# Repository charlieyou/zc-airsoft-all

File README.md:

# zc-airsoft-all

every design file from zc-airsoft, now open source

banshee lite circuit still needs some modifications to work, mainly adding resistors to fix outputs receiving conflicting input

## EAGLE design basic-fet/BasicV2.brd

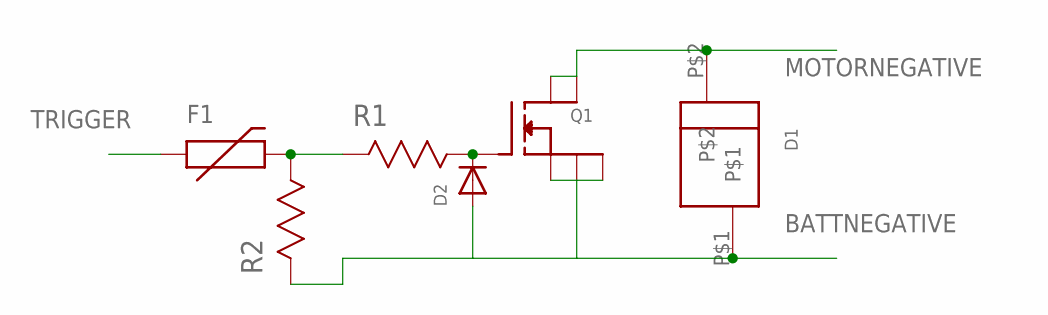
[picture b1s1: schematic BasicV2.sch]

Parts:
D1: 5.0SMDJ24ASMD; DO-214AB
D2: DIODESOD-123; SOD-123
F1: PTCSMD; PTC-1206
Q1: PSMN039LFPAC; LFPAC
R1: 100 Ohm; RESC3216X71N
R2: 220 Ohm; RESC6332X71N

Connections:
BATTNEGATIVE: D1.P$1, D2.A, Q1.1 (S1), Q1.2 (S2), Q1.3 (S3), R2.2 (R2)
MOTORNEGATIVE: D1.P$2, Q1.5 (D1), Q1.6 (D2)
unnamed: D2.C, Q1.4 (G), R1.1 (R1)
unnamed: F1.2, R1.2 (R2), R2.1 (R1)
TRIGGER: F1.1

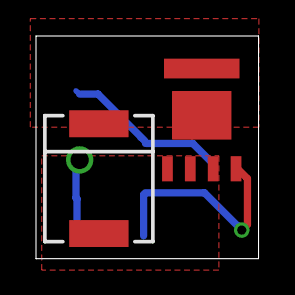
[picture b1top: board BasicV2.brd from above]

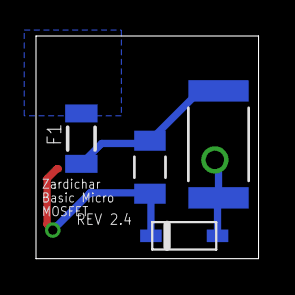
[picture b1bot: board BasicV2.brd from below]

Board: 2 copper layers, 12.4 x 12.4 mm, 6 parts (4 on the bottom side), 4 nets.

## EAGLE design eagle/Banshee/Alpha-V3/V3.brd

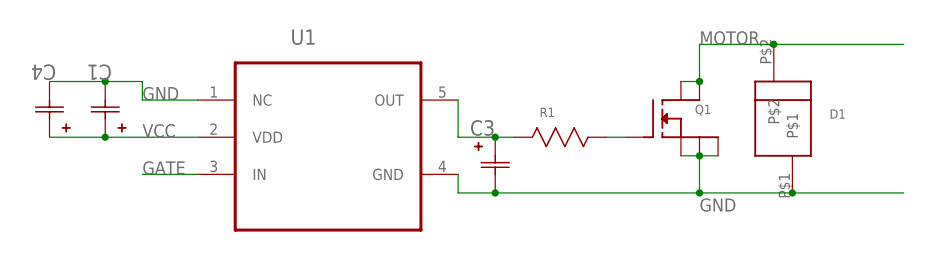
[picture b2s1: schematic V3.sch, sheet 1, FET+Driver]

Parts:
C1: 1UF; CAPC3216X127N
C3: 1uF; CAPC1608X94N
C4: 0.1UF; CAPC1608X90N
D1: 5.0SMDJ24ASMD; DO-214AB
Q1: PSMN039LFPAC; LFPAC; MPN PSMN0R9-25YLC,115
R1: 100 Ohm; RESC1608X60N
U1: NCS2001SN1T1G; SOT95P275X110-5N

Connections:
GATE: U1.3 (IN); also elsewhere on the board
GND: C1.2 (C2), C3.2 (C2), C4.2 (C2), D1.P$1, Q1.1 (S1), Q1.2 (S2), Q1.3 (S3), U1.1 (NC), U1.4 (GND); also elsewhere on the board
MOTOR: D1.P$2, Q1.5 (D1), Q1.6 (D2); also elsewhere on the board
unnamed: Q1.4 (G), R1.1 (R1)
unnamed: C3.1 (C1), R1.2 (R2), U1.5 (OUT)
VCC: C1.1 (C1), C4.1 (C1), U1.2 (VDD); also elsewhere on the board

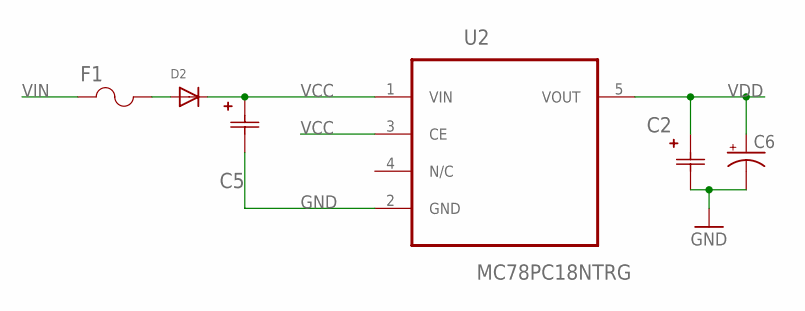
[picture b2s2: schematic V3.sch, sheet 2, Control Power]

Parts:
C2: 2200pF; CAPC1608X90N
C5: 220UF; CAPCP7343X430N
C6: 150uF; EIA3528
D2: DIODESOD-123; SOD-123
F1: F1206B3R00FWTR; FUSM3216X140N
U2: MC78PC18NTRG; SOT95P275X110-5N

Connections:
GND: C2.2 (C2), C5.2 (C2), C6.C (-), U2.2 (GND); also elsewhere on the board
unnamed: D2.A, F1.2
VCC: C5.1 (C1), D2.C, U2.1 (VIN), U2.3 (CE); also elsewhere on the board
VDD: C2.1 (C1), C6.A (+), U2.5 (VOUT); also elsewhere on the board
VIN: F1.1

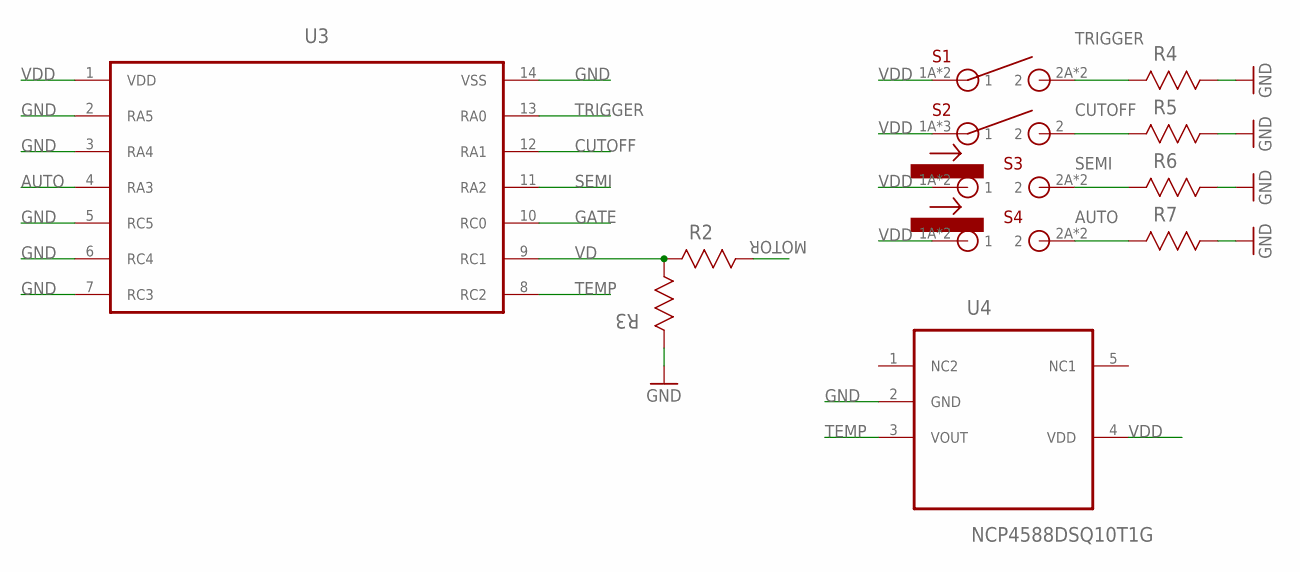
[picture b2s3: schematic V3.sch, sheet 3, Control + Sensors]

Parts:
R2: 15 kOhm; RESC1608X60N
R3, R4, R5, R6, R7: 4.7 kOhm; RESC1608X60N
S1: 7914S-1-000E
S2: ESE-31L15T
S3, S4: SPVM110100
U3: P89LPC912FDH,129; SOP65P640X110-14N
U4: NCP4588DSQ10T1G; SOT65P210X110-5N

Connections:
AUTO: R7.2 (R2), S4.2A (2), S4.2B (2), U3.4 (RA3)
CUTOFF: R5.2 (R2), S2.2, U3.12 (RA1)
GATE: U3.10 (RC0); also elsewhere on the board
GND: R3.2 (R2), R4.1 (R1), R5.1 (R1), R6.1 (R1), R7.1 (R1), U3.2 (RA5), U3.3 (RA4), U3.5 (RC5), U3.6 (RC4), U3.7 (RC3), U3.14 (VSS), U4.2 (GND); also elsewhere on the board
MOTOR: R2.1 (R1); also elsewhere on the board
NC2: U4.1 (NC2)
SEMI: R6.2 (R2), S3.2A (2), S3.2B (2), U3.11 (RA2)
TEMP: U3.8 (RC2), U4.3 (VOUT)
TRIGGER: R4.2 (R2), S1.2A (2), S1.2B (2), U3.13 (RA0)
VD: R2.2 (R2), R3.1 (R1), U3.9 (RC1)
VDD: S1.1A (1), S1.1B (1), S2.1A (1), S2.1B (1), S2.1C (1), S3.1A (1), S3.1B (1), S4.1A (1), S4.1B (1), U3.1 (VDD), U4.4 (VDD); also elsewhere on the board

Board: 4 copper layers, 25 parts (3 on the bottom side), 14 nets, no tracks yet.

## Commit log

2016-03-01 banshee alpha v3
2016-03-01 added banshee v3 files
2016-03-01 dimension board readme
2016-03-01 dimension board
2016-03-01 basic fet readme
2016-03-01 basic fet
2016-03-01 library readme
2016-03-01 library
2016-03-01 banshee readme
2016-03-01 banshee-lite

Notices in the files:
parts and their libraries:
SparkFun-PowerIC: Licensing: Creative Commons ShareAlike 4.0 International - https://creativecommons.org/licenses/by-sa/4.0
